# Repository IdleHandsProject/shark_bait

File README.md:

# SHARK BAIT

Check out the video using the Shark Bait Pumping System:

[Marks Channel](https://www.youtube.com/markrober)

For any questions regarding the project or parts please contact SeanHodginsYT@gmail.com

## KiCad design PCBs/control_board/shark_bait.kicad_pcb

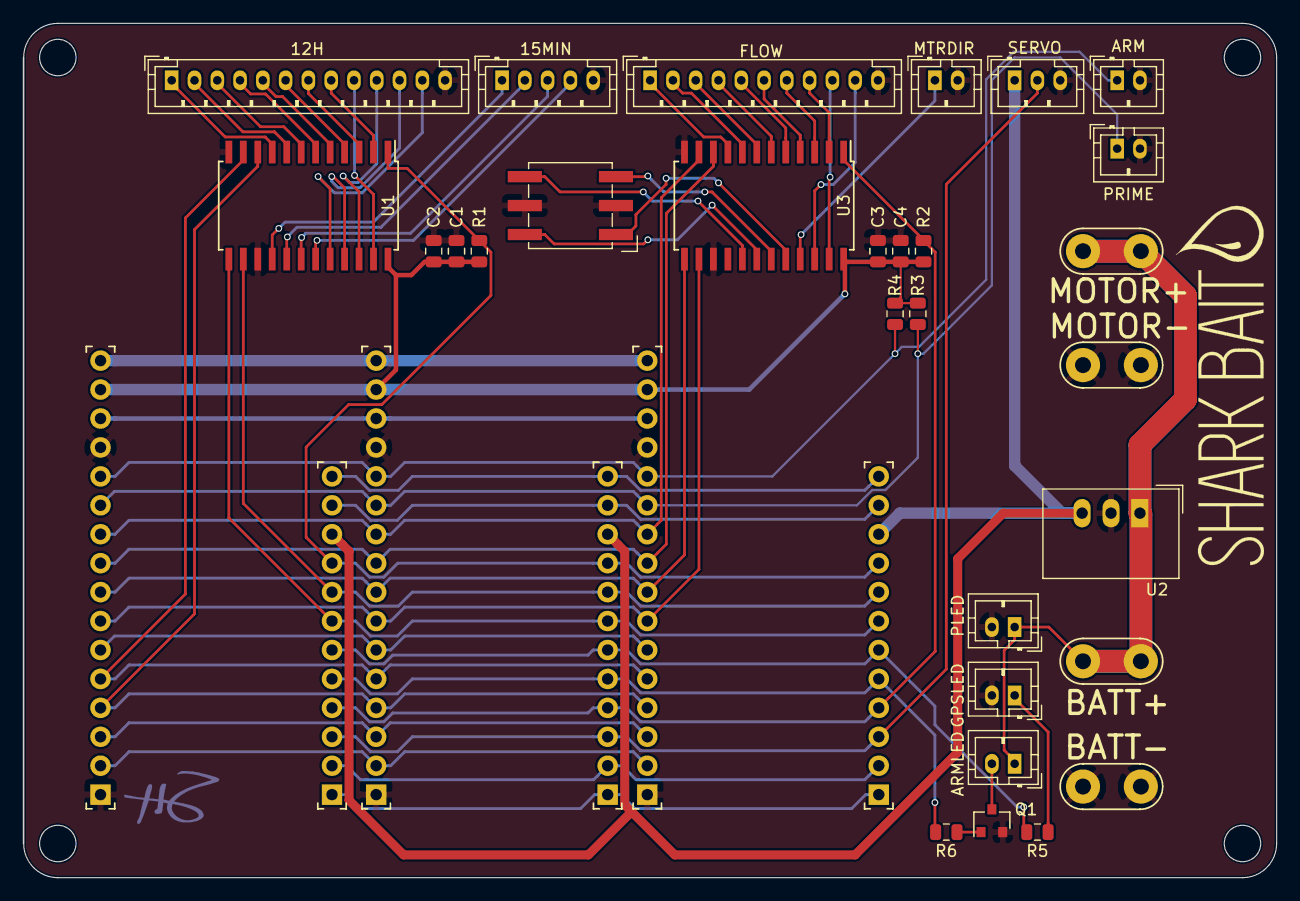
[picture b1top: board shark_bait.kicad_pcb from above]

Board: 2 copper layers, 110.0 x 74.9 mm, 38 parts (0 on the bottom side), 62 nets.

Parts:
C1, C2, C3, C4: 0.1uF; C_0805_2012Metric
J1: BATT+; connect_QC_Male
J2: BATT-; connect_QC_Male
J3: 15MIN; JST_PH_B5B-PH-K_1x05_P2.00mm_Vertical
J4: 12H; JST_PH_B13B-PH-K_1x13_P2.00mm_Vertical
J5: MTRDIR; JST_PH_B2B-PH-K_1x02_P2.00mm_Vertical
J6: FLOW; JST_PH_B11B-PH-K_1x11_P2.00mm_Vertical
J7: SERVO; JST_PH_B3B-PH-K_1x03_P2.00mm_Vertical
J8: MOTOR+; connect_QC_Male
J9: MOTOR-; connect_QC_Male
J10: PRIME; JST_PH_B2B-PH-K_1x02_P2.00mm_Vertical
J11: ARM; JST_PH_B2B-PH-K_1x02_P2.00mm_Vertical
J12: GPSLED; JST_PH_B2B-PH-K_1x02_P2.00mm_Vertical
J13: PLED; JST_PH_B2B-PH-K_1x02_P2.00mm_Vertical
J14: ARMLED; JST_PH_B2B-PH-K_1x02_P2.00mm_Vertical
J15: Conn_01x06; Nidec_CS-7
JP1, JP4, JP6: PinHeader_01x16_2.54mm; Conn_PinHeader_1x16_Reduced
JP2, JP3, JP5: PinHeader_01x12_2.54mm; Conn_PinHeader_1x12_Reduced
PCB**: VAL**; PCB_FeatherWing_NoHoles
PCB**#2, PCB**#3: VAL**; PCB_FeatherWing_NoHoles
Q1: MMBT3904; SOT-23
R1, R2, R3, R4: 10K; R_0805_2012Metric
R5: 330; R_0805_2012Metric
R6: 1k; R_0805_2012Metric
U1, U3: CD74HC4067M; SOIC-24W_7.5x15.4mm_P1.27mm
U2: TSR_1-2450; Converter_DCDC_TRACO_TSR-1_THT

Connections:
+5V: J7.1, JP2.10, JP3.10, JP5.10, U2.3
+BATT: J1.1, J8.1, J13.1, J14.1, U2.1
/A2: JP1.10, JP4.10, JP6.10, U3.11
/A3: JP1.9, JP4.9, JP6.9, U3.10
/A4: JP1.8, JP4.8, JP6.8, U3.13
/A5: JP1.7, JP4.7, JP6.7, U3.14
/AREF: JP1.14, JP4.14, JP6.14
/D0: JP1.3, JP4.3, JP6.3
/D1: JP1.2, JP4.2, JP6.2
/D6: JP2.4, JP3.4, JP5.4, R2.2, U3.1
/D11: JP2.7, JP3.7, JP5.7, U1.13
/D12: JP2.8, JP3.8, JP5.8, U1.14
/D13: JP2.9, JP3.9, JP5.9, R1.2, U1.1
/EN: JP2.11, JP3.11, JP5.11
/MISO: JP1.4, JP4.4, JP6.4, U1.10
/MOSI: JP1.5, JP4.5, JP6.5, U1.11
/SCK: JP1.6, JP4.6, JP6.6
/SCL: JP2.2, JP3.2, JP5.2
/SDA: JP2.1, JP3.1, JP5.1
/VBAT: JP2.12, JP3.12, JP5.12
/~RESET: JP1.16, JP4.16, JP6.16
ARM: J11.1, JP1.12, JP4.12, JP6.12, R4.2
ARMLED: JP2.5, JP3.5, JP5.5, R6.2
GND: C1.2, C2.2, C3.2, C4.2, J2.1, J3.5, J4.13, J5.2, J6.11, J7.3, J9.1, J10.2, J11.2, J12.2, J13.2, J15.2, J15.5, JP1.1, JP1.13, JP4.1, JP4.13, JP6.1, JP6.13, Q1.2, U1.12, U1.15, U2.2, U3.12, U3.15
GPSLED: JP2.6, JP3.6, JP5.6, R5.2
unnamed: J3.1, U1.16
unnamed: J3.2, U1.17
unnamed: J3.3, U1.18
unnamed: J3.4, U1.19
unnamed: J4.1, U1.9
unnamed: J4.2, U1.8
unnamed: J4.3, U1.7
unnamed: J4.4, U1.6
unnamed: J4.5, U1.5
unnamed: J4.6, U1.4
unnamed: J4.7, U1.3
unnamed: J4.8, U1.2
unnamed: J4.9, U1.23
unnamed: J4.10, U1.22
unnamed: J4.11, U1.21
unnamed: J4.12, U1.20
unnamed: J5.1, U3.21
unnamed: J6.1, U3.9
unnamed: J6.2, U3.8
unnamed: J6.3, U3.7
unnamed: J6.4, U3.6
unnamed: J6.5, U3.5
unnamed: J6.6, U3.4
unnamed: J6.7, U3.3
unnamed: J6.8, U3.2
unnamed: J6.9, U3.23
unnamed: J6.10, U3.22
unnamed: J12.1, R5.1
unnamed: J14.2, Q1.3
unnamed: J15.1, U3.20
unnamed: J15.3, U3.19
unnamed: J15.4, U3.18
unnamed: J15.6, U3.17
unnamed: Q1.1, R6.1
PRIME: J10.1, JP1.11, JP4.11, JP6.11, R3.2
Servo: J7.2, JP2.3, JP3.3, JP5.3
VCC: C1.1, C2.1, C3.1, C4.1, JP1.15, JP4.15, JP6.15, R1.1, R2.1, R3.1, R4.1, U1.24, U3.24

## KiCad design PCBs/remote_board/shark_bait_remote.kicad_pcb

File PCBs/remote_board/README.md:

# WIND Breakout

## wind makes the feather fly.

WIND is a breakout board for the Adafruit Feather Series to make it easier to fly wire and put together a project with little to no soldering. 

It contains a battery holder for a 18650(I hate loose batteries!), a few buttons, and 5 pin headers for each pin(plus a proto section). There is a power switch connected to the Enable pin(shuts off the regulator), and a voltage divider to the A0 analog 
for monitoring battery voltage.  

This makes it easy to mount in a housing, and wire up different sensors you want to test.

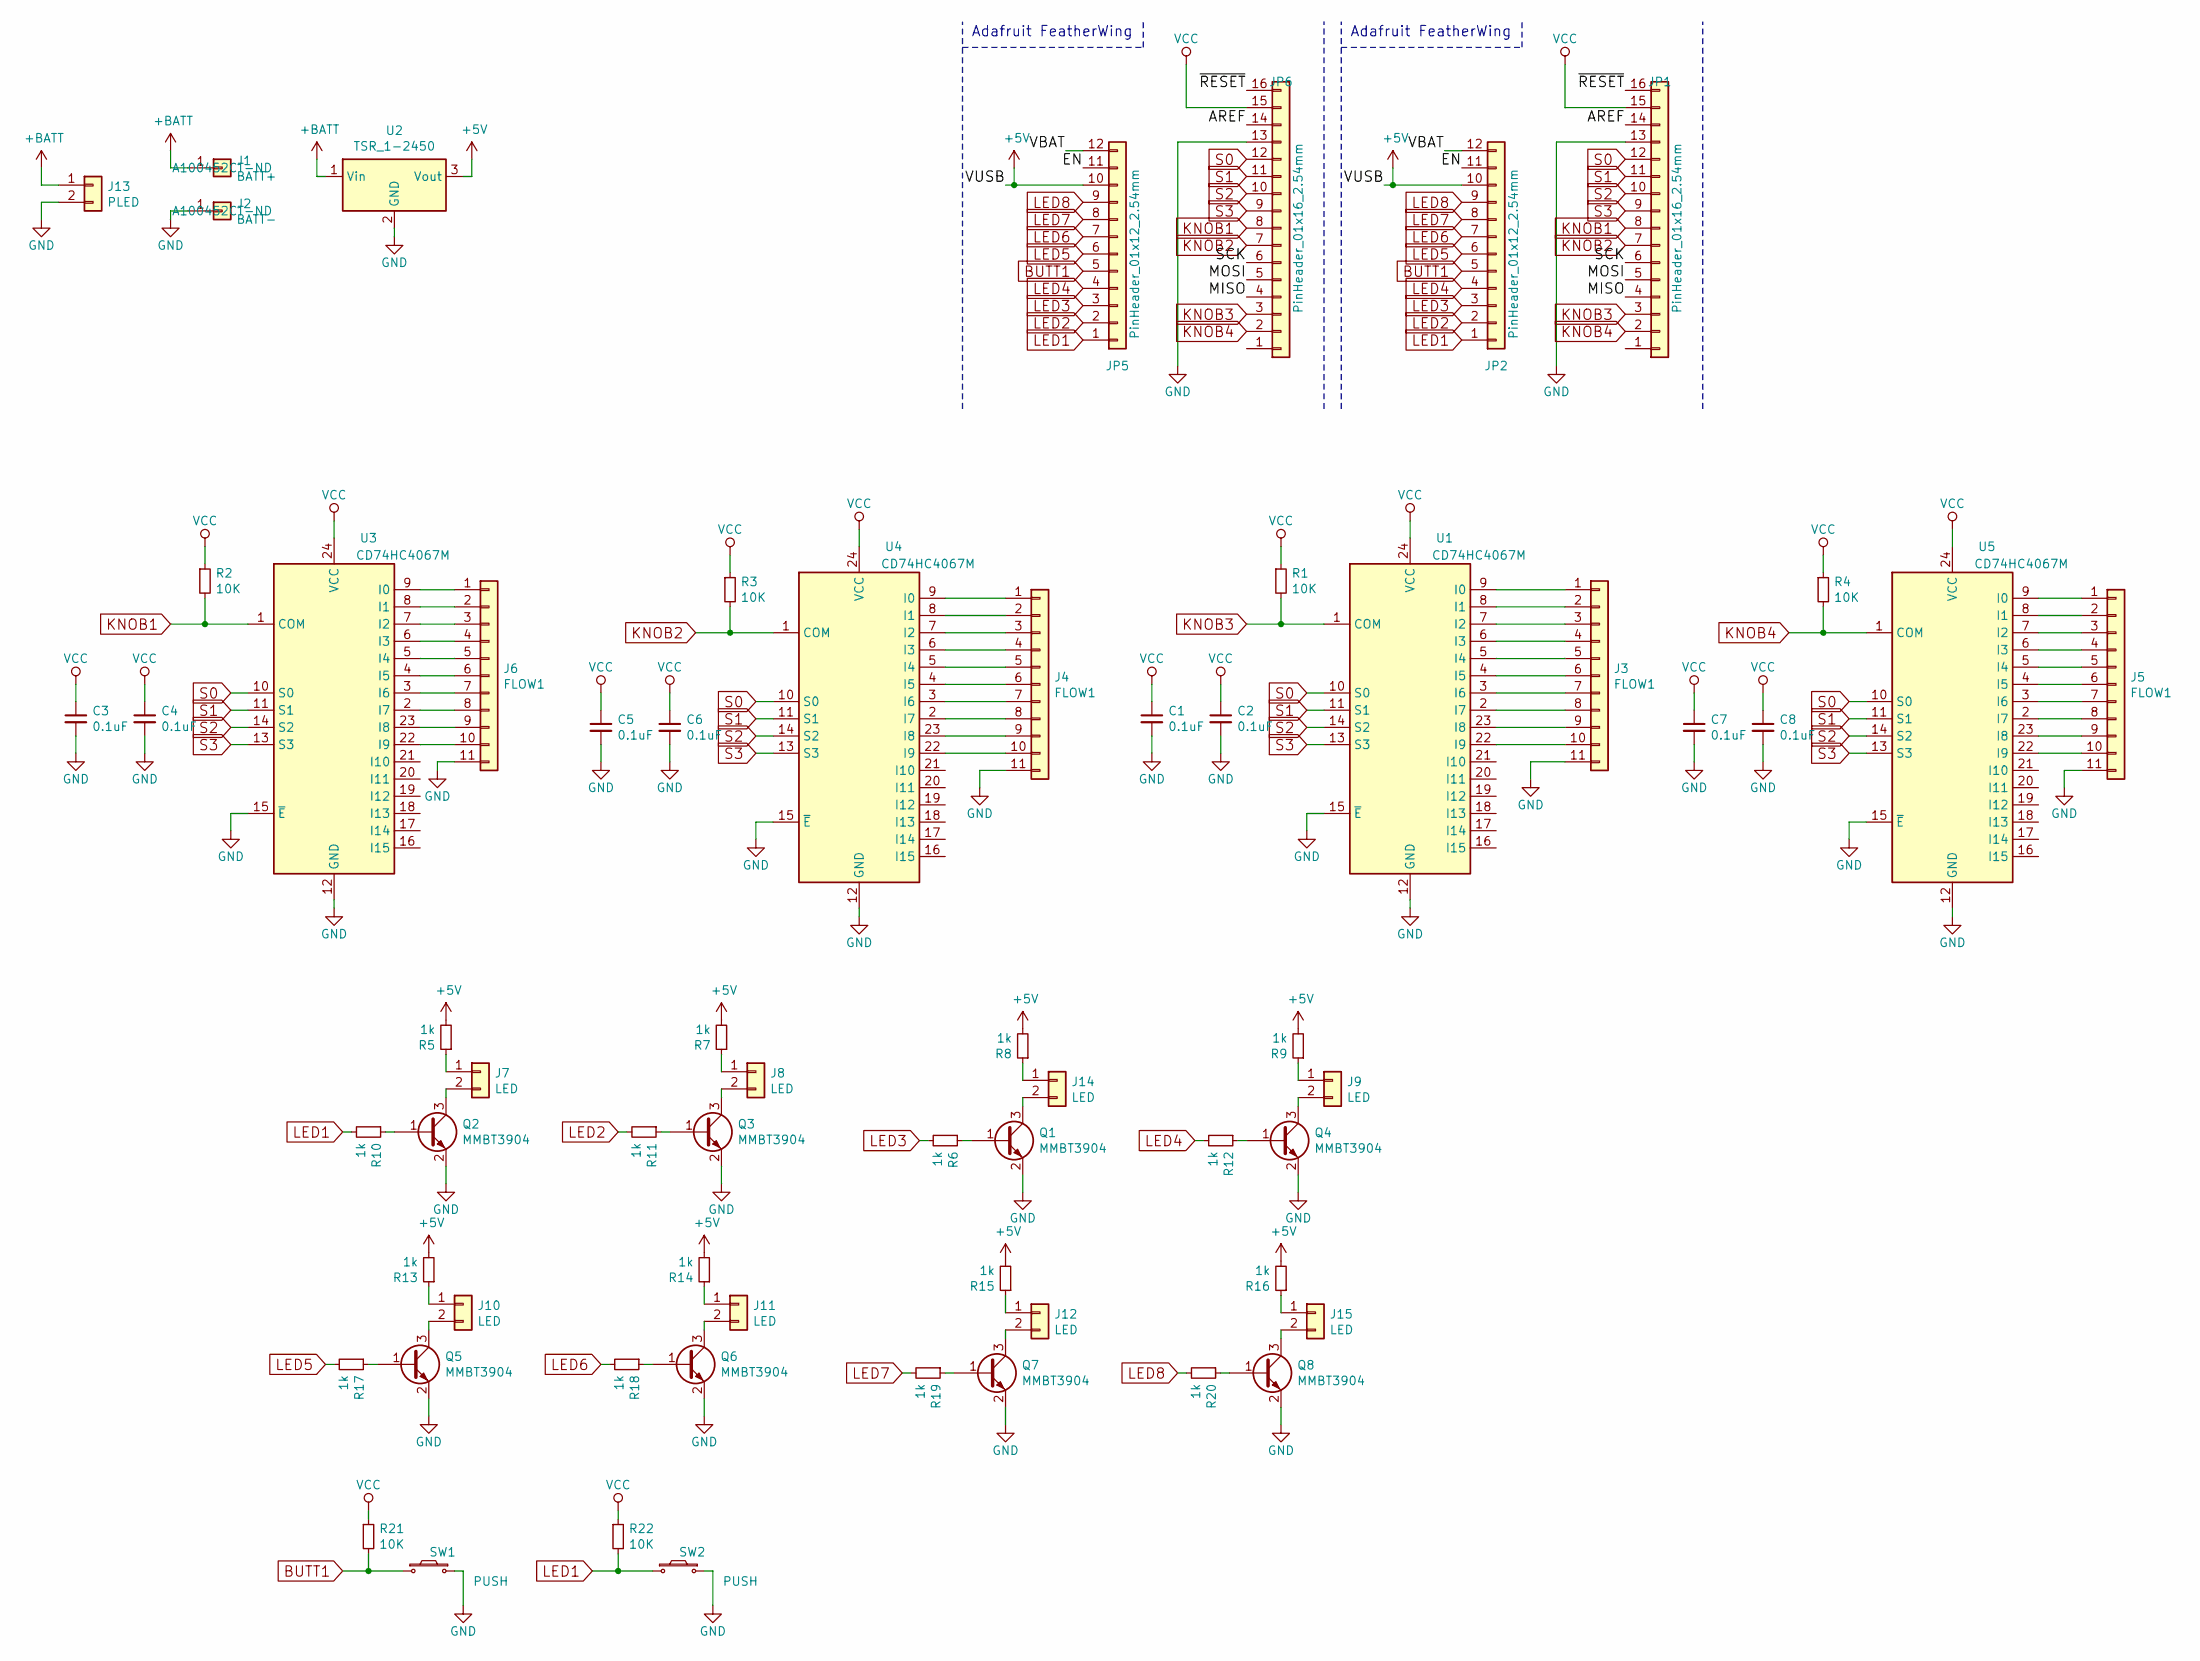
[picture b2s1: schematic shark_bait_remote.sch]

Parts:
C1, C2, C3, C4, C5, C6, C7, C8: 0.1uF; C_0805_2012Metric
J1: BATT+; connect_QC_Male; Digikey Part No. A100452CT-ND
J2: BATT-; connect_QC_Male; Digikey Part No. A100452CT-ND
J3, J4, J5, J6: FLOW1; JST_PH_B11B-PH-K_1x11_P2.00mm_Vertical
J7, J8, J9, J10, J11, J12, J14, J15: LED; JST_PH_B2B-PH-K_1x02_P2.00mm_Vertical
J13: PLED; JST_PH_B2B-PH-K_1x02_P2.00mm_Vertical
JP1, JP6: PinHeader_01x16_2.54mm; Conn_PinHeader_1x16_Reduced
JP2, JP5: PinHeader_01x12_2.54mm; Conn_PinHeader_1x12_Reduced
Q1, Q2, Q3, Q4, Q5, Q6, Q7, Q8: MMBT3904; SOT-23
R1, R2, R3, R4, R21, R22: 10K; R_0805_2012Metric
R5, R6, R7, R8, R9, R10, R11, R12, R13, R14, R15, R16, R17, R18, R19, R20: 1k; R_0805_2012Metric
SW1, SW2: PUSH; JST_PH_B2B-PH-K_1x02_P2.00mm_Vertical
U1, U3, U4, U5: CD74HC4067M; SOIC-24W_7.5x15.4mm_P1.27mm; Digikey Part No. 296-29408-1-ND
U2: TSR_1-2450; Converter_DCDC_TRACO_TSR-1_THT

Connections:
+5V: JP2.10, JP5.10, R5.2, R7.2, R8.2, R9.2, R13.2, R14.2, R15.2, R16.2, U2.3 (Vout)
+BATT: J1.1, J13.1, U2.1 (Vin)
/AREF: JP1.14, JP6.14
/EN: JP2.11, JP5.11
/MISO: JP1.4, JP6.4
/MOSI: JP1.5, JP6.5
/SCK: JP1.6, JP6.6
/VBAT: JP2.12, JP5.12
/~RESET: JP1.16, JP6.16
BUTT1: JP2.5, JP5.5, R21.2, SW1.1
GND: C1.2, C2.2, C3.2, C4.2, C5.2, C6.2, C7.2, C8.2, J2.1, J3.11, J4.11, J5.11, J6.11, J13.2, JP1.1, JP1.13, JP6.1, JP6.13, Q1.2 (E), Q2.2 (E), Q3.2 (E), Q4.2 (E), Q5.2 (E), Q6.2 (E), Q7.2 (E), Q8.2 (E), SW1.2, SW2.2, U1.12 (GND), U1.15 (~E), U2.2 (GND), U3.12 (GND), U3.15 (~E), U4.12 (GND), U4.15 (~E), U5.12 (GND), U5.15 (~E)
KNOB1: JP1.8, JP6.8, R2.2, U3.1 (COM)
KNOB2: JP1.7, JP6.7, R3.2, U4.1 (COM)
KNOB3: JP1.3, JP6.3, R1.2, U1.1 (COM)
KNOB4: JP1.2, JP6.2, R4.2, U5.1 (COM)
LED1: JP2.1, JP5.1, R10.2, R22.2, SW2.1
LED2: JP2.2, JP5.2, R11.2
LED3: JP2.3, JP5.3, R6.2
LED4: JP2.4, JP5.4, R12.2
LED5: JP2.6, JP5.6, R17.2
LED6: JP2.7, JP5.7, R18.2
LED7: JP2.8, JP5.8, R19.2
LED8: JP2.9, JP5.9, R20.2
unnamed: J3.1, U1.9 (I0)
unnamed: J3.2, U1.8 (I1)
unnamed: J3.3, U1.7 (I2)
unnamed: J3.4, U1.6 (I3)
unnamed: J3.5, U1.5 (I4)
unnamed: J3.6, U1.4 (I5)
unnamed: J3.7, U1.3 (I6)
unnamed: J3.8, U1.2 (I7)
unnamed: J3.9, U1.23 (I8)
unnamed: J3.10, U1.22 (I9)
unnamed: J4.1, U4.9 (I0)
unnamed: J4.2, U4.8 (I1)
unnamed: J4.3, U4.7 (I2)
unnamed: J4.4, U4.6 (I3)
unnamed: J4.5, U4.5 (I4)
unnamed: J4.6, U4.4 (I5)
unnamed: J4.7, U4.3 (I6)
unnamed: J4.8, U4.2 (I7)
unnamed: J4.9, U4.23 (I8)
unnamed: J4.10, U4.22 (I9)
unnamed: J5.1, U5.9 (I0)
unnamed: J5.2, U5.8 (I1)
unnamed: J5.3, U5.7 (I2)
unnamed: J5.4, U5.6 (I3)
unnamed: J5.5, U5.5 (I4)
unnamed: J5.6, U5.4 (I5)
unnamed: J5.7, U5.3 (I6)
unnamed: J5.8, U5.2 (I7)
unnamed: J5.9, U5.23 (I8)
unnamed: J5.10, U5.22 (I9)
unnamed: J6.1, U3.9 (I0)
unnamed: J6.2, U3.8 (I1)
unnamed: J6.3, U3.7 (I2)
unnamed: J6.4, U3.6 (I3)
unnamed: J6.5, U3.5 (I4)
unnamed: J6.6, U3.4 (I5)
unnamed: J6.7, U3.3 (I6)
unnamed: J6.8, U3.2 (I7)
unnamed: J6.9, U3.23 (I8)
unnamed: J6.10, U3.22 (I9)
unnamed: J7.1, R5.1
unnamed: J7.2, Q2.3 (C)
unnamed: J8.1, R7.1
unnamed: J8.2, Q3.3 (C)
unnamed: J9.1, R9.1
unnamed: J9.2, Q4.3 (C)
unnamed: J10.1, R13.1
unnamed: J10.2, Q5.3 (C)
unnamed: J11.1, R14.1
unnamed: J11.2, Q6.3 (C)
unnamed: J12.1, R15.1
unnamed: J12.2, Q7.3 (C)
unnamed: J14.1, R8.1
unnamed: J14.2, Q1.3 (C)
unnamed: J15.1, R16.1
unnamed: J15.2, Q8.3 (C)
unnamed: Q1.1 (B), R6.1
unnamed: Q2.1 (B), R10.1
unnamed: Q3.1 (B), R11.1
unnamed: Q4.1 (B), R12.1
unnamed: Q5.1 (B), R17.1
unnamed: Q6.1 (B), R18.1
unnamed: Q7.1 (B), R19.1
unnamed: Q8.1 (B), R20.1
S0: JP1.12, JP6.12, U1.10 (S0), U3.10 (S0), U4.10 (S0), U5.10 (S0)
S1: JP1.11, JP6.11, U1.11 (S1), U3.11 (S1), U4.11 (S1), U5.11 (S1)
S2: JP1.10, JP6.10, U1.14 (S2), U3.14 (S2), U4.14 (S2), U5.14 (S2)
S3: JP1.9, JP6.9, U1.13 (S3), U3.13 (S3), U4.13 (S3), U5.13 (S3)
VCC: C1.1, C2.1, C3.1, C4.1, C5.1, C6.1, C7.1, C8.1, JP1.15, JP6.15, R1.1, R2.1, R3.1, R4.1, R21.1, R22.1, U1.24 (VCC), U3.24 (VCC), U4.24 (VCC), U5.24 (VCC)

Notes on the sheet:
Adafruit FeatherWing

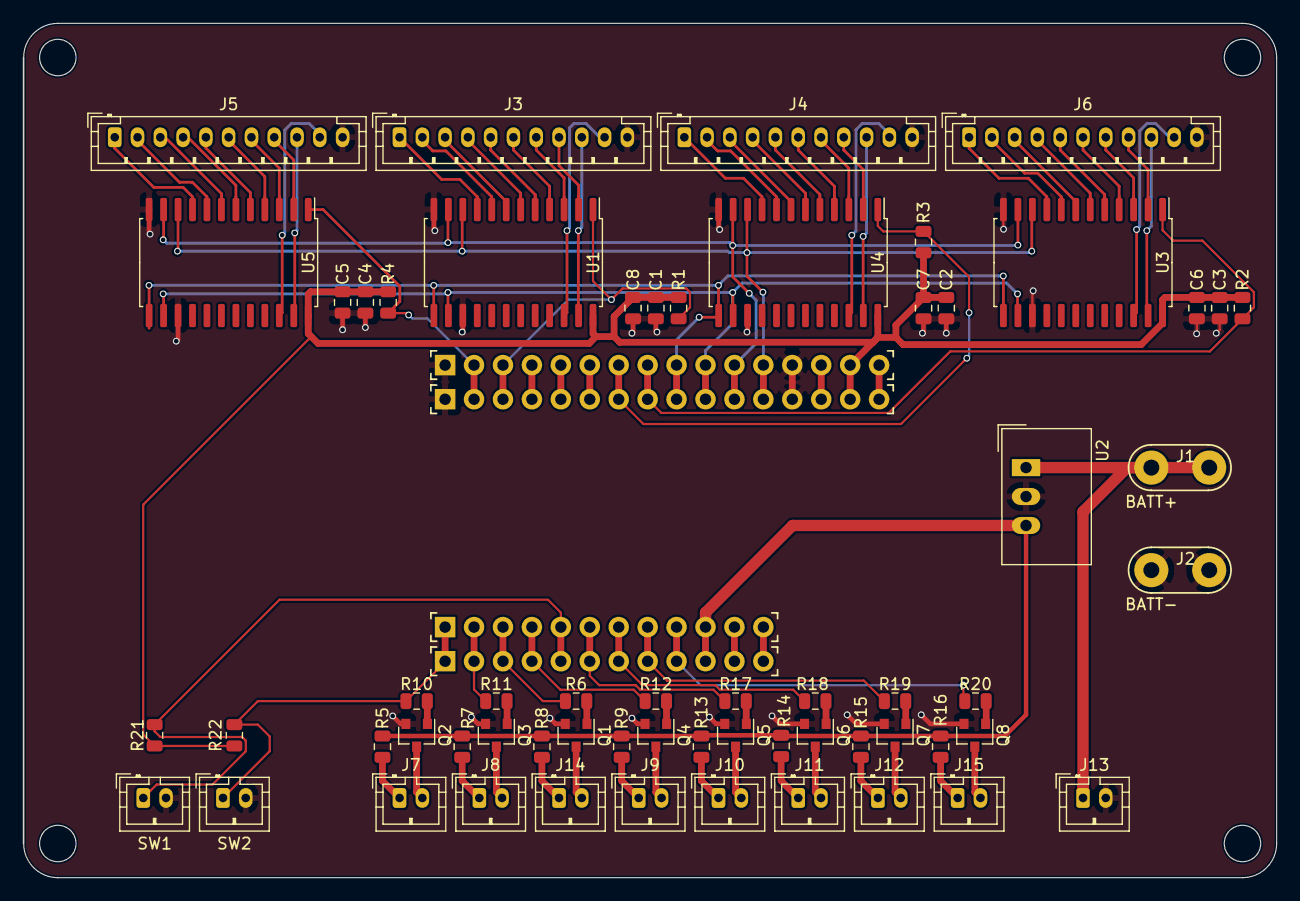
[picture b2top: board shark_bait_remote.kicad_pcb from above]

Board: 2 copper layers, 110.0 x 74.9 mm, 65 parts (0 on the bottom side), 92 nets.

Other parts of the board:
PCB**: VAL**; PCB_FeatherWing_NoHoles

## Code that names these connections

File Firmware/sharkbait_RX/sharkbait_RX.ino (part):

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unsigned long startTime = 0;
unsigned long pumpTime = 0;

#define PRIME A1
#define ARM A0
#define ARMLED 9
#define SERVO 5
#define LIMIT 5
#define MINUTES 60000
#define SECONDS 1000
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  pinMode(LED, OUTPUT);
  pinMode(RFM95_RST, OUTPUT);
  digitalWrite(RFM95_RST, HIGH);
  pinMode(ARM, INPUT_PULLUP);
  pinMode(ARMLED, OUTPUT);
  digitalWrite(ARMLED, LOW);
  pinMode(PRIME, INPUT_PULLUP);
  pinMode(com, INPUT);
  for (int x = 0; x < 4; x++) {
    pinMode(s[x], OUTPUT);
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#endif


  // IF YOU START WITH ARM SWITCH ACTIVE IT WILL MANUALLY OVERRIDE THE RF SIGNAL AND START PUMPING IN ONE HOUR DEPENDING ON SET FLOW RATE
  int OVERRIDE = !(digitalRead(ARM));
  unsigned int sorTime = millis();
  unsigned int eorTime = millis();
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
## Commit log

2019-07-24 added PDF Manual
2019-07-24 Delete Manual.ai
    Don't need AI files on GitHub
2019-07-28 no more AI file
